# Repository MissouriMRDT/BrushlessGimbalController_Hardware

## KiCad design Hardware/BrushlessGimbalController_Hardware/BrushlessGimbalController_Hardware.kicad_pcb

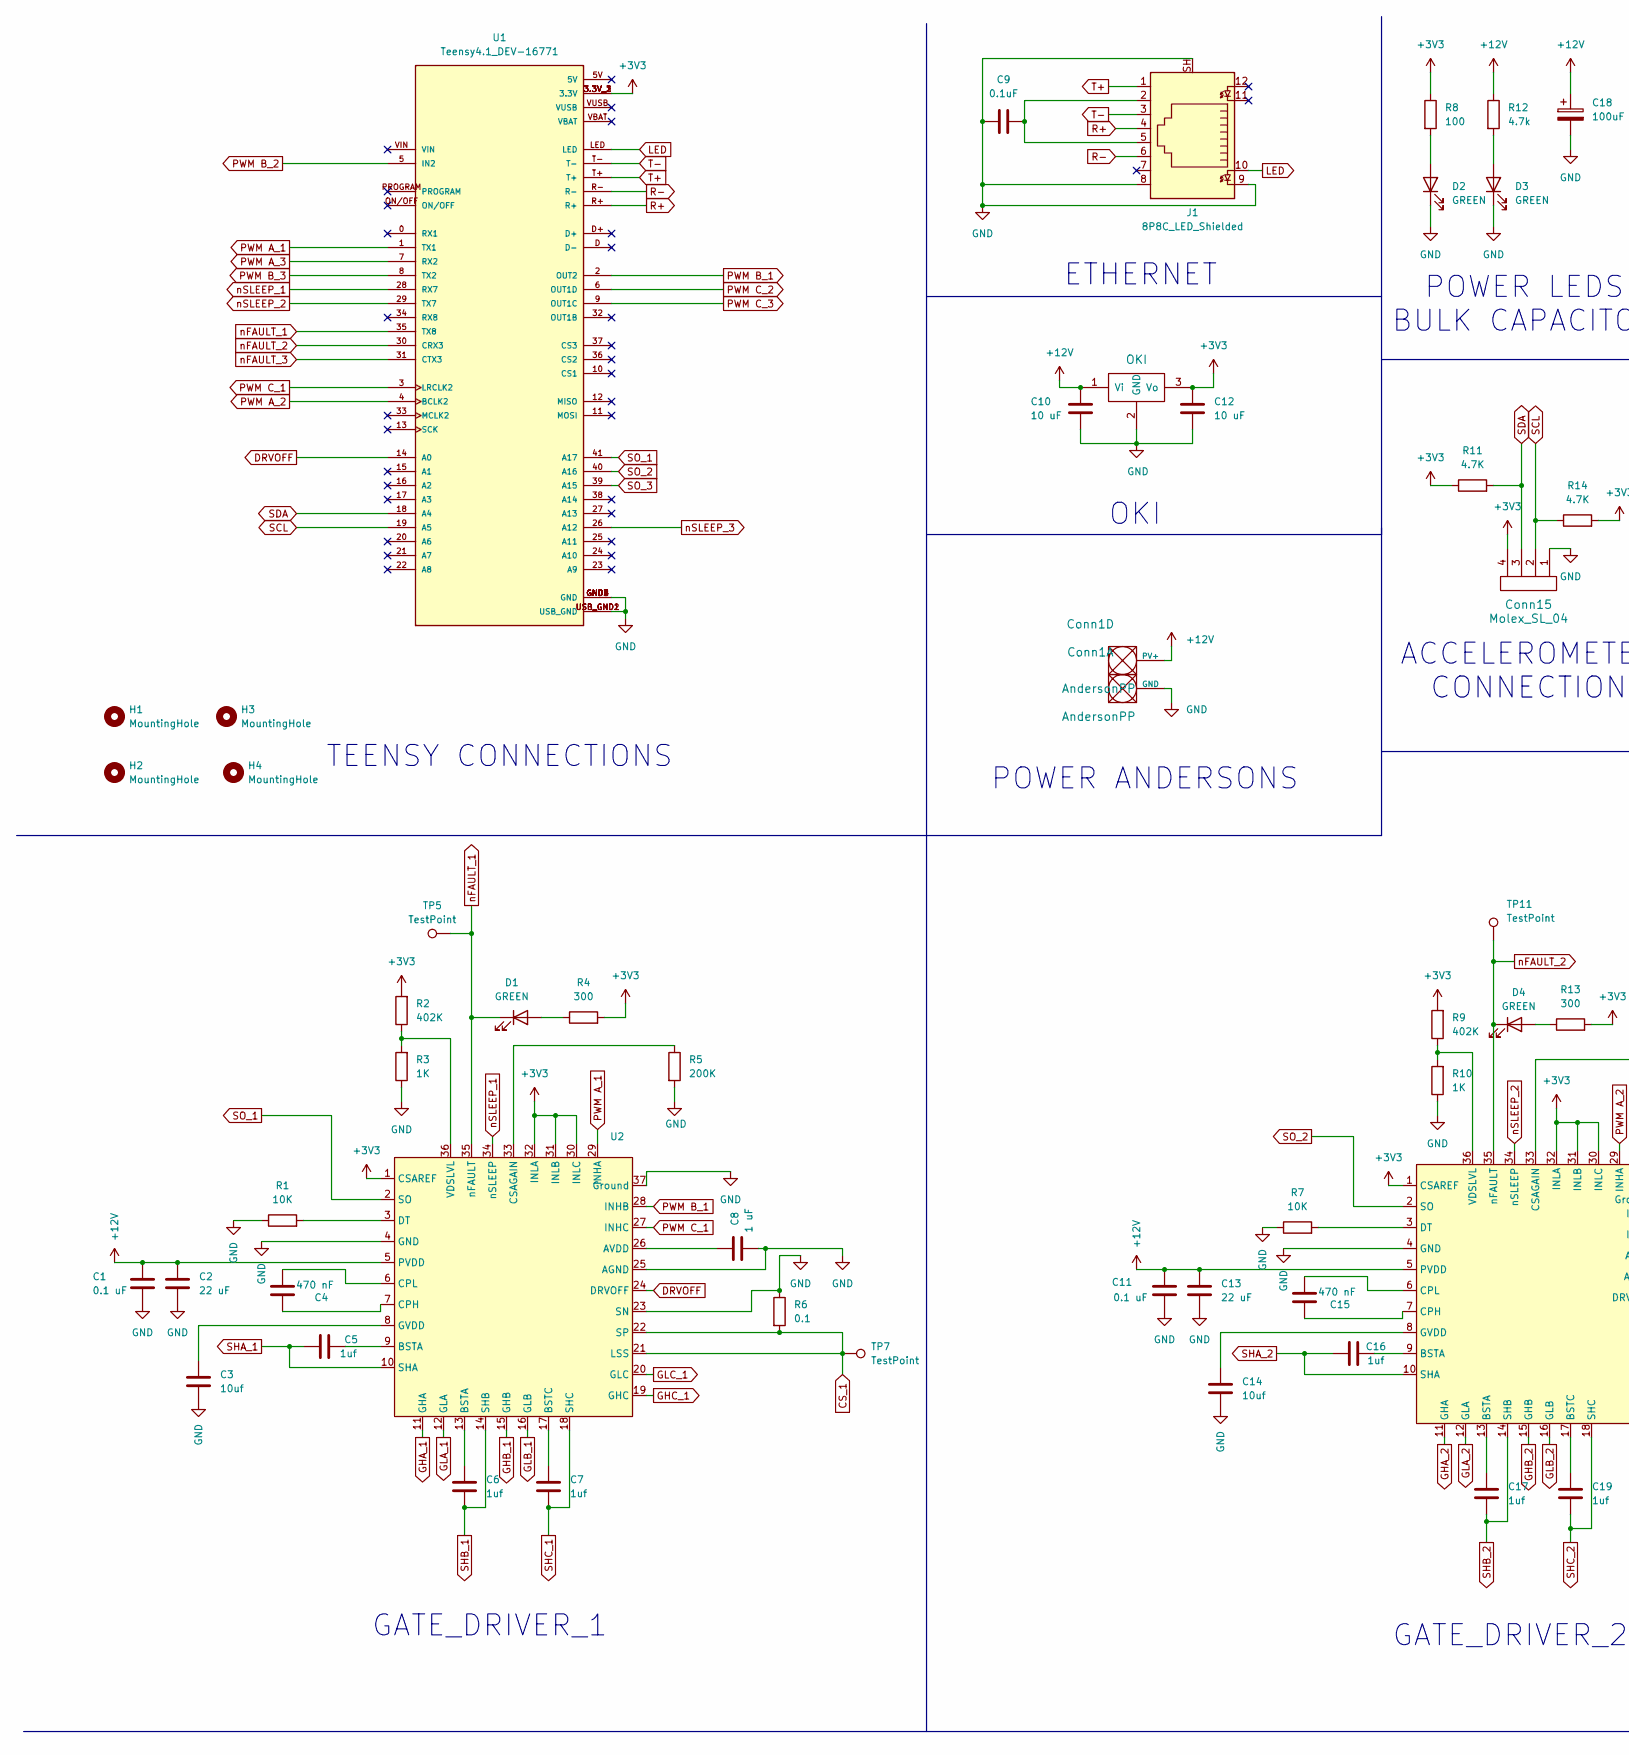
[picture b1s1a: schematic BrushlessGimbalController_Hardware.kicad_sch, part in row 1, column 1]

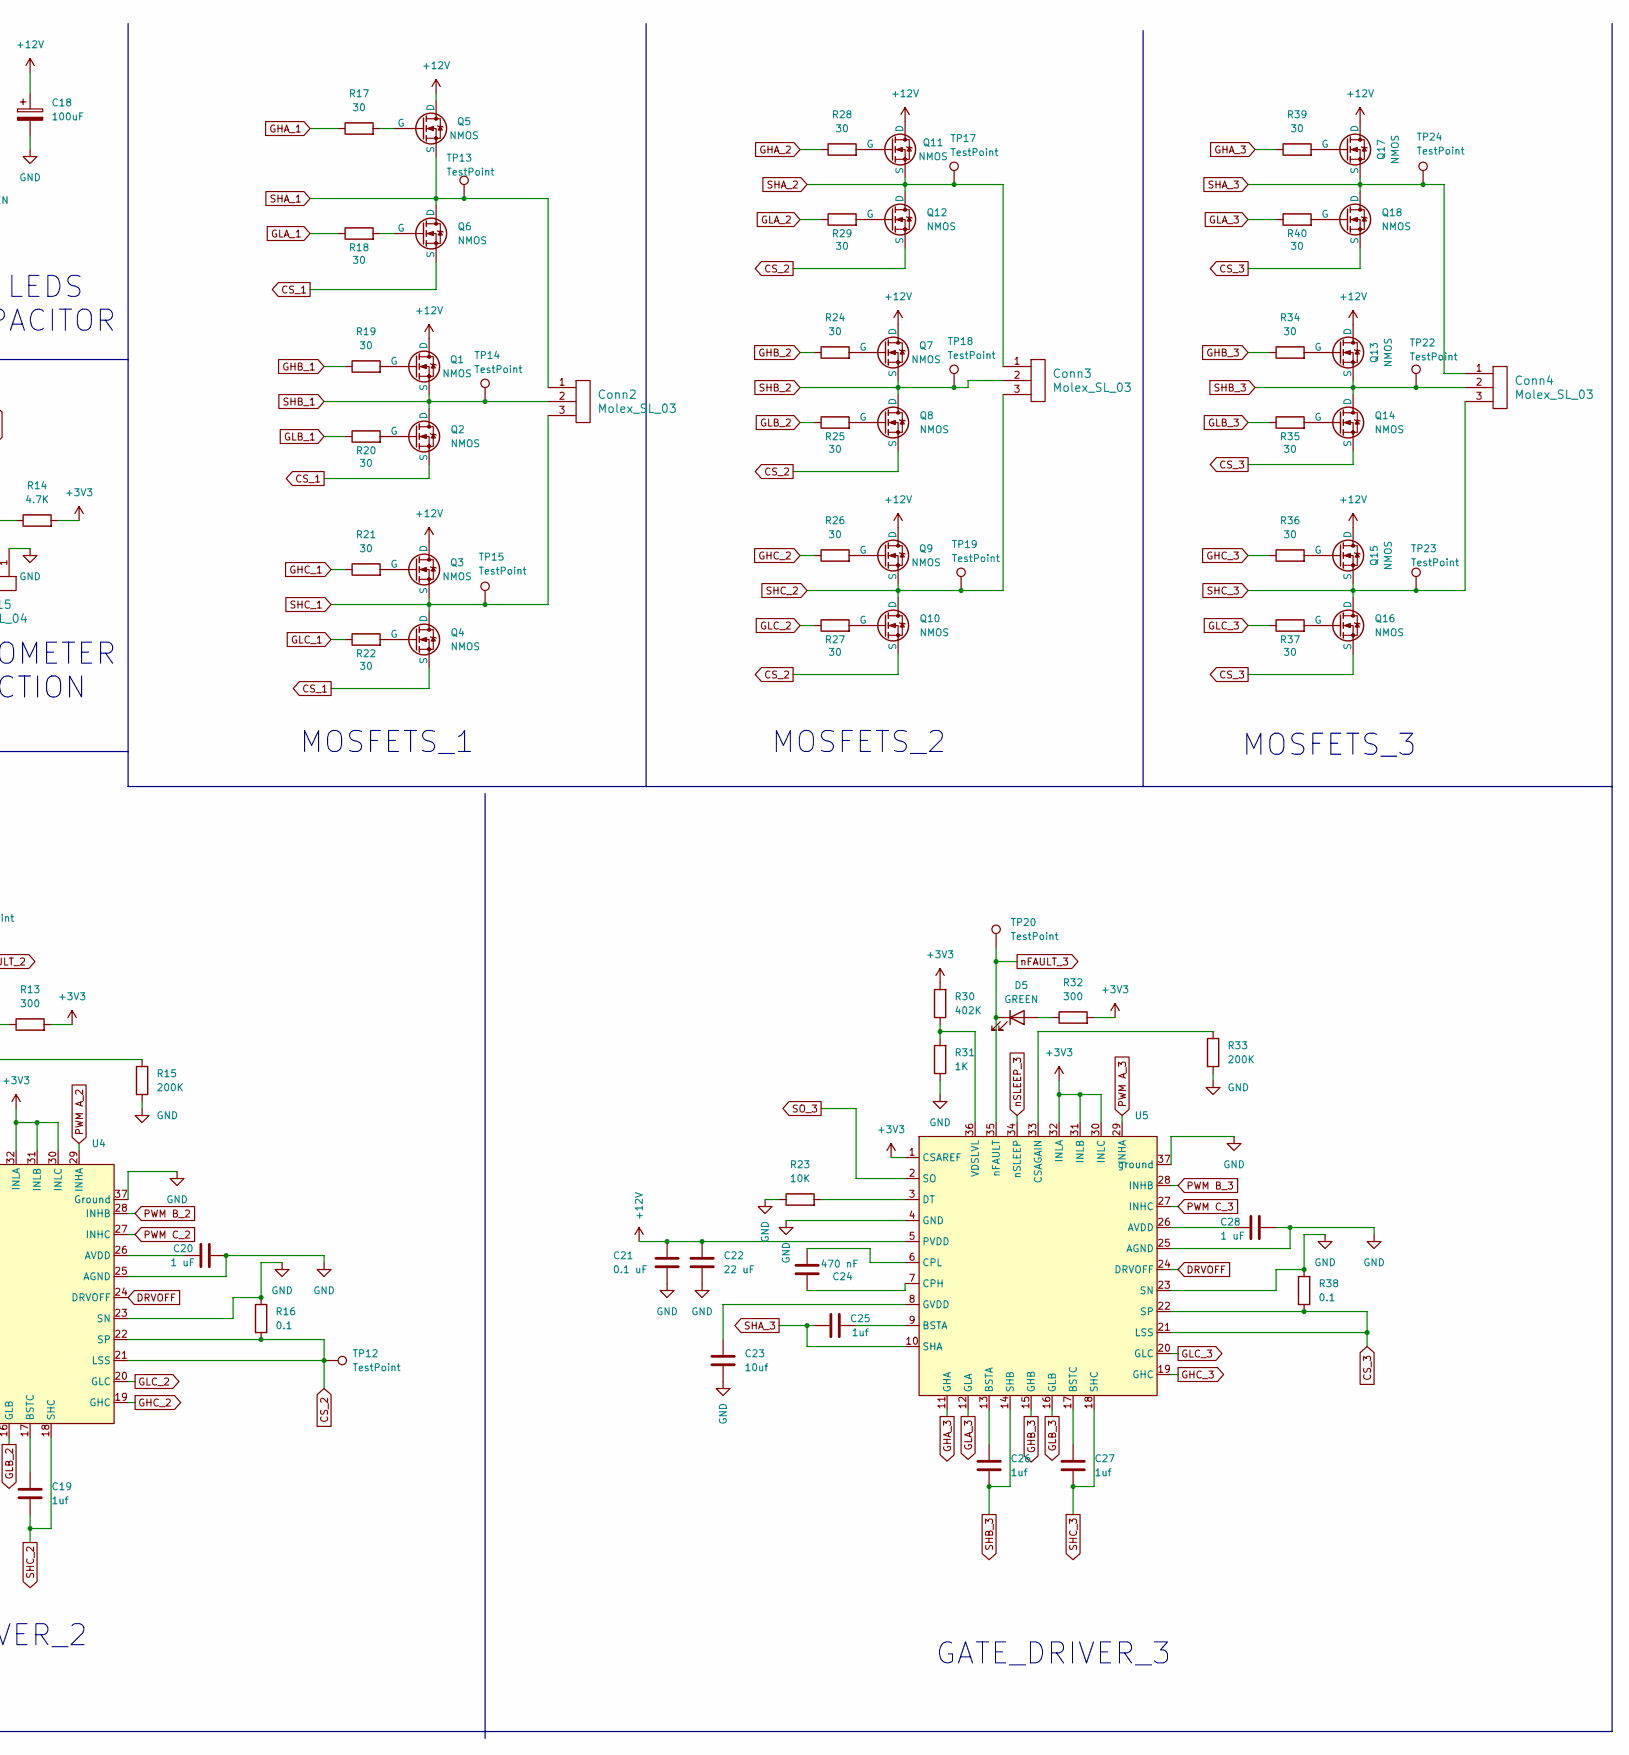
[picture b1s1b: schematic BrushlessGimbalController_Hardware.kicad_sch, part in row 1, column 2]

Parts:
C1, C11, C21: 0.1 uF; C_0603_1608Metric_Pad1.08x0.95mm_HandSolder
C2, C13, C22: 22 uF; CP_Radial_D5.0mm_P2.00mm
C3, C14, C23: 10uf; C_0603_1608Metric_Pad1.08x0.95mm_HandSolder
C4, C15, C24: 470 nF; C_0603_1608Metric_Pad1.08x0.95mm_HandSolder
C5, C6, C7, C16, C17, C19, C25, C26, C27: 1uf; C_0603_1608Metric_Pad1.08x0.95mm_HandSolder
C8, C20, C28: 1 uF; C_0603_1608Metric_Pad1.08x0.95mm_HandSolder
C9: 0.1uF; C_0603_1608Metric_Pad1.08x0.95mm_HandSolder
C10, C12: 10 uF; C_0603_1608Metric_Pad1.08x0.95mm_HandSolder
C18: 100uF; C_Radial_D6.3mm_H5.0mm_P2.50mm
Conn1: AndersonPP; Square_Anderson_2_H_Side_By_Side
Conn2, Conn3, Conn4: Molex_SL_03; Molex_SL_171971-0003_1x03_P2.54mm_Vertical
Conn15: Molex_SL_04; MOLEX_SL_04_Vertical
D1, D2, D3, D4, D5: GREEN; LED_0603_1608Metric_Pad1.05x0.95mm_HandSolder
H1, H2, H3, H4: MountingHole; MountingHole_3mm
J1: 8P8C_LED_Shielded; RJ45_Teensy
Q1, Q2, Q3, Q4, Q5, Q6, Q7, Q8, Q9, Q10, Q11, Q12, Q13, Q14, Q15, Q16, Q17, Q18: NMOS; SOT-23-3
R1, R7, R23: 10K; R_0603_1608Metric_Pad0.98x0.95mm_HandSolder
R2, R9, R30: 402K; R_0603_1608Metric_Pad0.98x0.95mm_HandSolder
R3, R10, R31: 1K; R_0603_1608Metric_Pad0.98x0.95mm_HandSolder
R4, R13, R32: 300; R_0603_1608Metric_Pad0.98x0.95mm_HandSolder
R5, R15, R33: 200K; R_0603_1608Metric_Pad0.98x0.95mm_HandSolder
R6, R16, R38: 0.1; R_2816_7142Metric_Pad3.20x4.45mm_HandSolder
R8: 100; R_0603_1608Metric_Pad0.98x0.95mm_HandSolder
R11, R14: 4.7K; R_0603_1608Metric_Pad0.98x0.95mm_HandSolder
R12: 4.7k; R_0603_1608Metric_Pad0.98x0.95mm_HandSolder
R17, R18, R19, R20, R21, R22, R24, R25, R26, R27, R28, R29, R34, R35, R36, R37, R39, R40: 30; R_0603_1608Metric_Pad0.98x0.95mm_HandSolder
TP5, TP7, TP11, TP12, TP13, TP14, TP15, TP17, TP18, TP19, TP20, TP22, TP23, TP24: TestPoint; TestPoint_Pad_D2.0mm
U1: Teensy4.1_DEV-16771; Teensy_4_1; PARTREV 4.1
U2, U4, U5: REE0036A-IPC_A
U3: OKI; Converter_DCDC_Murata_OKI-78SR_Horizontal

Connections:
+3V3: C12.1, Conn15.4, R2.2, R4.2, R8.1, R9.2, R11.1, R13.2, R14.2, R30.2, R32.2, U1.3.3V_1 (3.3V), U1.3.3V_2 (3.3V), U1.3.3V_3 (3.3V), U2.1 (CSAREF), U2.30 (INLC), U2.31 (INLB), U2.32 (INLA), U3.3 (Vo), U4.1 (CSAREF), U4.30 (INLC), U4.31 (INLB), U4.32 (INLA), U5.1 (CSAREF), U5.30 (INLC), U5.31 (INLB), U5.32 (INLA)
+12V: C1.2, C2.2, C10.1, C11.2, C13.2, C18.1, C21.2, C22.2, Conn1.2 (PV+), Q1.1 (D), Q3.1 (D), Q5.1 (D), Q7.1 (D), Q9.1 (D), Q11.1 (D), Q13.1 (D), Q15.1 (D), Q17.1 (D), R12.1, U2.5 (PVDD), U3.1 (Vi), U4.5 (PVDD), U5.5 (PVDD)
CS_1: Q2.3 (S), Q4.3 (S), Q6.3 (S), R6.2, TP7.1, U2.21 (LSS), U2.22 (SP)
CS_2: Q8.3 (S), Q10.3 (S), Q12.3 (S), R16.2, TP12.1, U4.21 (LSS), U4.22 (SP)
CS_3: Q14.3 (S), Q16.3 (S), Q18.3 (S), R38.2, U5.21 (LSS), U5.22 (SP); also elsewhere on the board
DRVOFF: U1.14 (A0), U2.24 (DRVOFF), U4.24 (DRVOFF), U5.24 (DRVOFF)
GHA_1: R17.1, U2.11 (GHA)
GHA_2: R28.1, U4.11 (GHA)
GHA_3: R39.1, U5.11 (GHA)
GHB_1: R19.1, U2.15 (GHB)
GHB_2: R24.1, U4.15 (GHB)
GHB_3: R34.1, U5.15 (GHB)
GHC_1: R21.1, U2.19 (GHC)
GHC_2: R26.1, U4.19 (GHC)
GHC_3: R36.1, U5.19 (GHC)
GLA_1: R18.1, U2.12 (GLA)
GLA_2: R29.1, U4.12 (GLA)
GLA_3: R40.1, U5.12 (GLA)
GLB_1: R20.1, U2.16 (GLB)
GLB_2: R25.1, U4.16 (GLB)
GLB_3: R35.1, U5.16 (GLB)
GLC_1: R22.1, U2.20 (GLC)
GLC_2: R27.1, U4.20 (GLC)
GLC_3: R37.1, U5.20 (GLC)
GND: C1.1, C2.1, C3.2, C8.1, C9.1, C10.2, C11.1, C12.2, C13.1, C14.2, C18.2, C20.1, C21.1, C22.1, C23.2, C28.1, Conn1.1 (GND), Conn15.1, D2.1 (K), D3.1 (K), J1.8, J1.9, J1.SH, R1.1, R3.1, R5.2, R6.1, R7.1, R10.1, R15.2, R16.1, R23.1, R31.1, R33.2, R38.1, U1.GND1 (GND), U1.GND2 (GND), U1.GND3 (GND), U1.GND4 (GND), U1.GND5 (GND), U1.USB_GND1 (USB_GND), U1.USB_GND2 (USB_GND), U2.4 (GND), U2.23 (SN), U2.25 (AGND), U2.37 (Ground), U3.2 (GND), U4.4 (GND), U4.23 (SN), U4.25 (AGND), U4.37 (Ground), U5.4 (GND), U5.23 (SN), U5.25 (AGND), U5.37 (ground)
LED: J1.10, U1.LED
unnamed: C5.1, U2.9 (BSTA)
unnamed: C6.1, U2.13 (BSTA)
unnamed: C9.2, J1.2, J1.5
unnamed: C16.1, U4.9 (BSTA)
unnamed: C17.1, U4.13 (BSTA)
unnamed: C25.2, U5.9 (BSTA)
unnamed: C26.1, U5.13 (BSTA)
unnamed: D1.2 (A), R4.1
unnamed: D2.2 (A), R8.2
unnamed: D3.2 (A), R12.2
unnamed: D4.2 (A), R13.1
unnamed: D5.2 (A), R32.1
unnamed: Q1.2 (G), R19.2
unnamed: Q2.2 (G), R20.2
unnamed: Q3.2 (G), R21.2
unnamed: Q4.2 (G), R22.2
unnamed: Q5.2 (G), R17.2
unnamed: Q6.2 (G), R18.2
unnamed: Q7.2 (G), R24.2
unnamed: Q8.2 (G), R25.2
unnamed: Q9.2 (G), R26.2
unnamed: Q10.2 (G), R27.2
unnamed: Q11.2 (G), R28.2
unnamed: Q12.2 (G), R29.2
unnamed: Q13.2 (G), R34.2
unnamed: Q14.2 (G), R35.2
unnamed: Q15.2 (G), R36.2
unnamed: Q16.2 (G), R37.2
unnamed: Q17.2 (G), R39.2
unnamed: Q18.2 (G), R40.2
unnamed: C8.2, U2.26 (AVDD)
unnamed: C7.1, U2.17 (BSTC)
unnamed: C4.2, U2.7 (CPH)
unnamed: C4.1, U2.6 (CPL)
unnamed: R5.1, U2.33 (CSAGAIN)
unnamed: R1.2, U2.3 (DT)
unnamed: C3.1, U2.8 (GVDD)
unnamed: R2.1, R3.2, U2.36 (VDSLVL)
unnamed: C20.2, U4.26 (AVDD)
unnamed: C19.1, U4.17 (BSTC)
unnamed: C15.2, U4.7 (CPH)
unnamed: C15.1, U4.6 (CPL)
unnamed: R15.1, U4.33 (CSAGAIN)
unnamed: R7.2, U4.3 (DT)
unnamed: C14.1, U4.8 (GVDD)
unnamed: R9.1, R10.2, U4.36 (VDSLVL)
unnamed: C28.2, U5.26 (AVDD)
unnamed: C27.1, U5.17 (BSTC)
unnamed: C24.2, U5.7 (CPH)
unnamed: C24.1, U5.6 (CPL)
unnamed: R33.1, U5.33 (CSAGAIN)
unnamed: R23.2, U5.3 (DT)
unnamed: C23.1, U5.8 (GVDD)
unnamed: R30.1, R31.2, U5.36 (VDSLVL)
PWM A_1: U1.1 (TX1), U2.29 (INHA)
PWM A_2: U1.4 (BCLK2), U4.29 (INHA)
PWM A_3: U1.7 (RX2), U5.29 (INHA)
PWM B_1: U1.2 (OUT2), U2.28 (INHB)
PWM B_2: U1.5 (IN2), U4.28 (INHB)
PWM B_3: U1.8 (TX2), U5.28 (INHB)
PWM C_1: U1.3 (LRCLK2), U2.27 (INHC)
PWM C_2: U1.6 (OUT1D), U4.27 (INHC)
PWM C_3: U1.9 (OUT1C), U5.27 (INHC)
R+: J1.4, U1.R+
R-: J1.6, U1.R-
SCL: Conn15.2, R14.1, U1.19 (A5)
SDA: Conn15.3, R11.2, U1.18 (A4)
SHA_1: C5.2, Conn2.1, Q5.3 (S), Q6.1 (D), TP13.1, U2.10 (SHA)
SHA_2: C16.2, Conn3.1, Q11.3 (S), Q12.1 (D), TP17.1, U4.10 (SHA)
SHA_3: C25.1, Conn4.1, Q17.3 (S), Q18.1 (D), TP24.1, U5.10 (SHA)
SHB_1: C6.2, Conn2.2, Q1.3 (S), Q2.1 (D), TP14.1, U2.14 (SHB)
SHB_2: C17.2, Conn3.2, Q7.3 (S), Q8.1 (D), TP18.1, U4.14 (SHB)
SHB_3: C26.2, Conn4.2, Q13.3 (S), Q14.1 (D), TP22.1, U5.14 (SHB)
SHC_1: C7.2, Conn2.3, Q3.3 (S), Q4.1 (D), TP15.1, U2.18 (SHC)
SHC_2: C19.2, Conn3.3, Q9.3 (S), Q10.1 (D), TP19.1, U4.18 (SHC)
SHC_3: C27.2, Conn4.3, Q15.3 (S), Q16.1 (D), TP23.1, U5.18 (SHC)
SO_1: U1.41 (A17), U2.2 (SO)
SO_2: U1.40 (A16), U4.2 (SO)
SO_3: U1.39 (A15), U5.2 (SO)
T+: J1.1, U1.T+
T-: J1.3, U1.T-
nFAULT_1: D1.1 (K), TP5.1, U1.35 (TX8), U2.35 (nFAULT)
nFAULT_2: D4.1 (K), TP11.1, U1.30 (CRX3), U4.35 (nFAULT)
nFAULT_3: D5.1 (K), TP20.1, U1.31 (CTX3), U5.35 (nFAULT)
nSLEEP_1: U1.28 (RX7), U2.34 (nSLEEP)
nSLEEP_2: U1.29 (TX7), U4.34 (nSLEEP)
nSLEEP_3: U1.26 (A12), U5.34 (nSLEEP)

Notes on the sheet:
GATE_DRIVER_3
TEENSY CONNECTIONS
MOSFETS_1
POWER ANDERSONS
POWER LEDS BULK CAPACITOR
GATE_DRIVER_1
ACCELEROMETER CONNECTION
MOSFETS_2
MOSFETS_3
ETHERNET
GATE_DRIVER_2
OKI

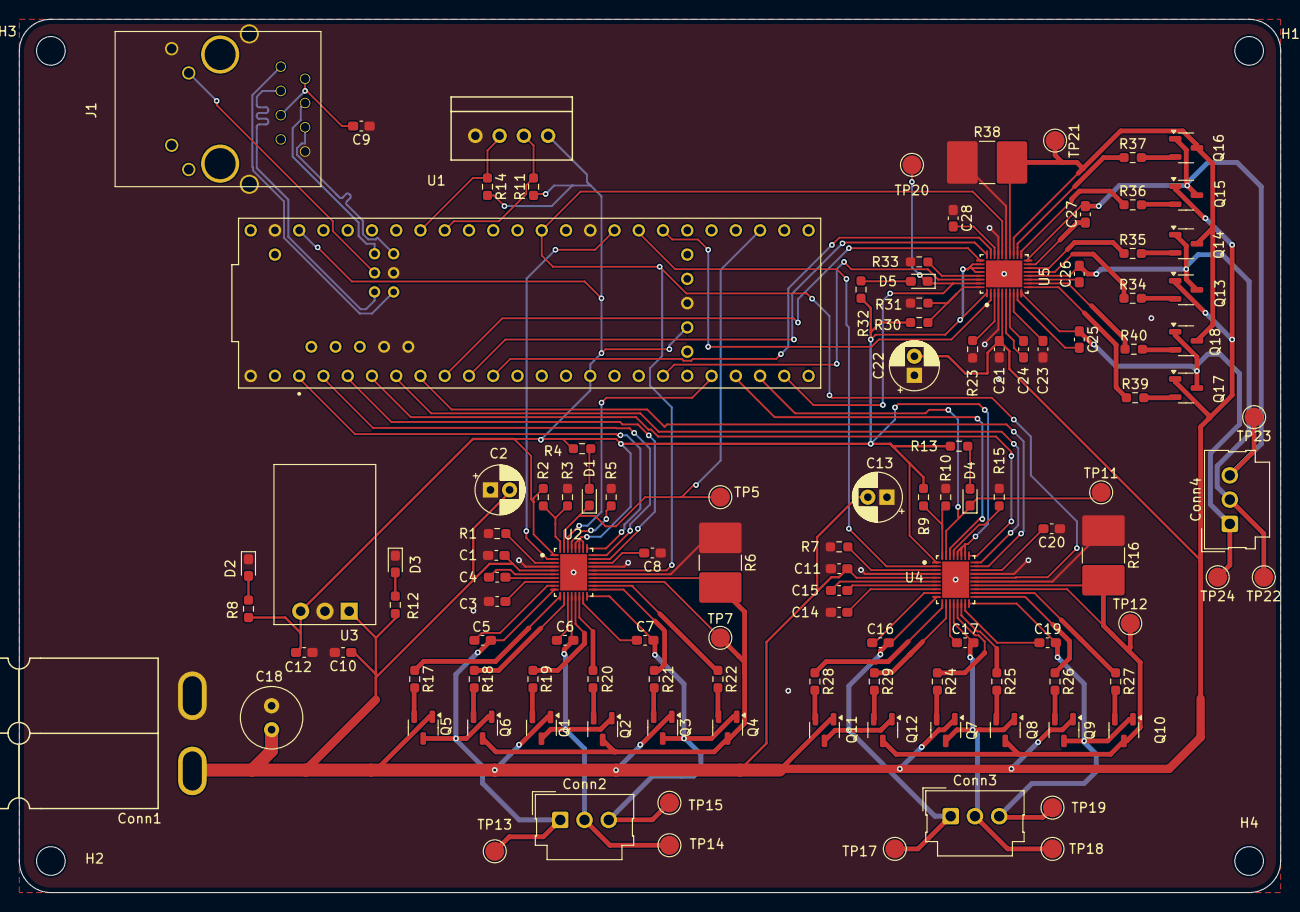
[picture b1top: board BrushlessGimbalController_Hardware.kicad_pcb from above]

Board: 2 copper layers, 132.1 x 91.4 mm, 121 parts (0 on the bottom side), 113 nets.

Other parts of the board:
TP21: TestPoint; TestPoint_Pad_D2.0mm

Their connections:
CS_3: TP21.1; also elsewhere on the board

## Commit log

2024-11-14 Schematic or something
    real
2024-11-14 Added datasheet
    real
2024-11-14 filepath
    to be fixed
2024-11-14 Un-f*cking the files
2024-11-14 Un-fucking files pt.2
2025-01-17 Layout Ready For Review
    Added all of the traces and ground planes and vias and things
2025-01-21 Layout revisions
    Layout revisions implemented from conversation with Drew
    Edge cuts added
    Vias added to ground planes
    Ethernet connector moved to not attach to Teensey
    Hopefully ready for order whenever next board order date is
2025-01-23 Garrett Changes
    Fixed some stray disconnected traces
    Added mounting holes to schematic
    Flipped ethernet port placement 180 degrees
    Adjusted skew on Ethernet differential pairs
    Replaced 470nf capacitor with correct 0603 ceramic capacitor (Was 470 uf and electrolytic)
    Removed test points measurable directly from Teensey or Andersons
2025-01-25 Final changes before ordering (hopefully)
    Added a pin for the ground pad in the middle of the microcontrollers so it would actually connect to ground
    Also added a via to the ground pad in the middle of the microcontroller because the schematic example had some
    Put vias on some other non-connected ground plane areas
2025-01-25 gerber files and BOM
    made a zip folder for Gerber files
    generated BOM
